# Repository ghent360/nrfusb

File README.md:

# Theory of operation #

A transmitter and receiver must be programmed with identical 32 bit
radio IDs.  With those IDs, the transmitter and receiver select a set of
23 channels using a pseudorandom number generator.

## Channel Selection ##

23 channels are selected.  Their selection and order is determined as
follows:

The pseudorandom number function is:

```
prn = (prn * 0x0019660D) + 0x3C6EF35F
```

A potential channel is `prn % 125`.  Channels are evaluated in order such that:

* The prn is evaluated once, then modulo 125 to generate a candidate
  channel

* No channel is repeated.  If the candidate channel has already been
  selected, the candidate is discarded.

* No more than a certain number of channels can be chosen from each of
  the different bands.  If a candidate channel would exceed this
  limit, it is discarded.
  * 0-31: 6
  * 32-63: 6
  * 64-95: 6
  * 96-125: 5

## Transmission ##

The transmitter and receiver use the nrf24l01 Enhanced ShockBurst with
the following parameters:

* 5 byte address field, the channel ID mapped into 5 bytes as below
* Dynamic payload length
* 2 byte CRC
* No automatic retransmission
* Auto acknowledgement
* 1Mbps data rate

The transmitter sends a new packet every 20ms, waiting 1ms for an
acknowledgement with data on the same channel.  Each transmitted
packet advances to the next channel in the channel selected list,
wrapping around.

## Reception ##

To initially lock onto a transmitter, the receiver picks a random
channel from the list and listens for 20 channel change times (0.4s).
If no packet is received, it then moves to the next channel in the
list and waits another 20 time periods, continuing this process until
a packet is received.  Once a packet is received it switches to the
following procedure.

In normal reception, immediately after receiving and acknowledging a
packet, the receiver switches to the next channel in the list.  It
waits at least 22ms for the next packet to be received.  If no packet
is received, then the channel is switched to the next one and
listening recommences.  If 5 packets in a row are missed, then the
receiver returns to the initial lock procedure.

## ID selection ##

The ShockBurst address is derived from the 32 bit ID as follows.

1100bbbb bbbbbbbH bbbbbbbH bbbbbbbH bbbbbbH

`b` is a bit from the 32 bit ID.

The `H` bits are selected to be the opposite of whatever the
preceeding bit was.

Rationale: The highest bits are defined to be distinct from the
preamble, which consists of alternating bits.  The H bits are present
to reduce the likelihood that random noise will cause the address to
be identified by the baseband receiver.

## Scheduling ##

The transmitter and receiver have 15 different "slots" to hold
outgoing data.  Each can be configured for a different priority or
transmission rate and each can hold up to 16 bytes of data.

The transmission rate/priority is configured by providing a 32 bit
bitmask denoting in which timeslots this slot should be sent.
Configuring an infeasible set of slots will result in unspecified data
being sent at a lower rate.

A priority of 0 is the default, which signifies that the slot should
not be transmitted.  0xffffffff implies it should be sent every
timeslot.  0x55555555 would be every other timeslot, etc.

The data in a slot will continue to be transmitted at the specified
frequency whether or not it has been updated by the client recently.

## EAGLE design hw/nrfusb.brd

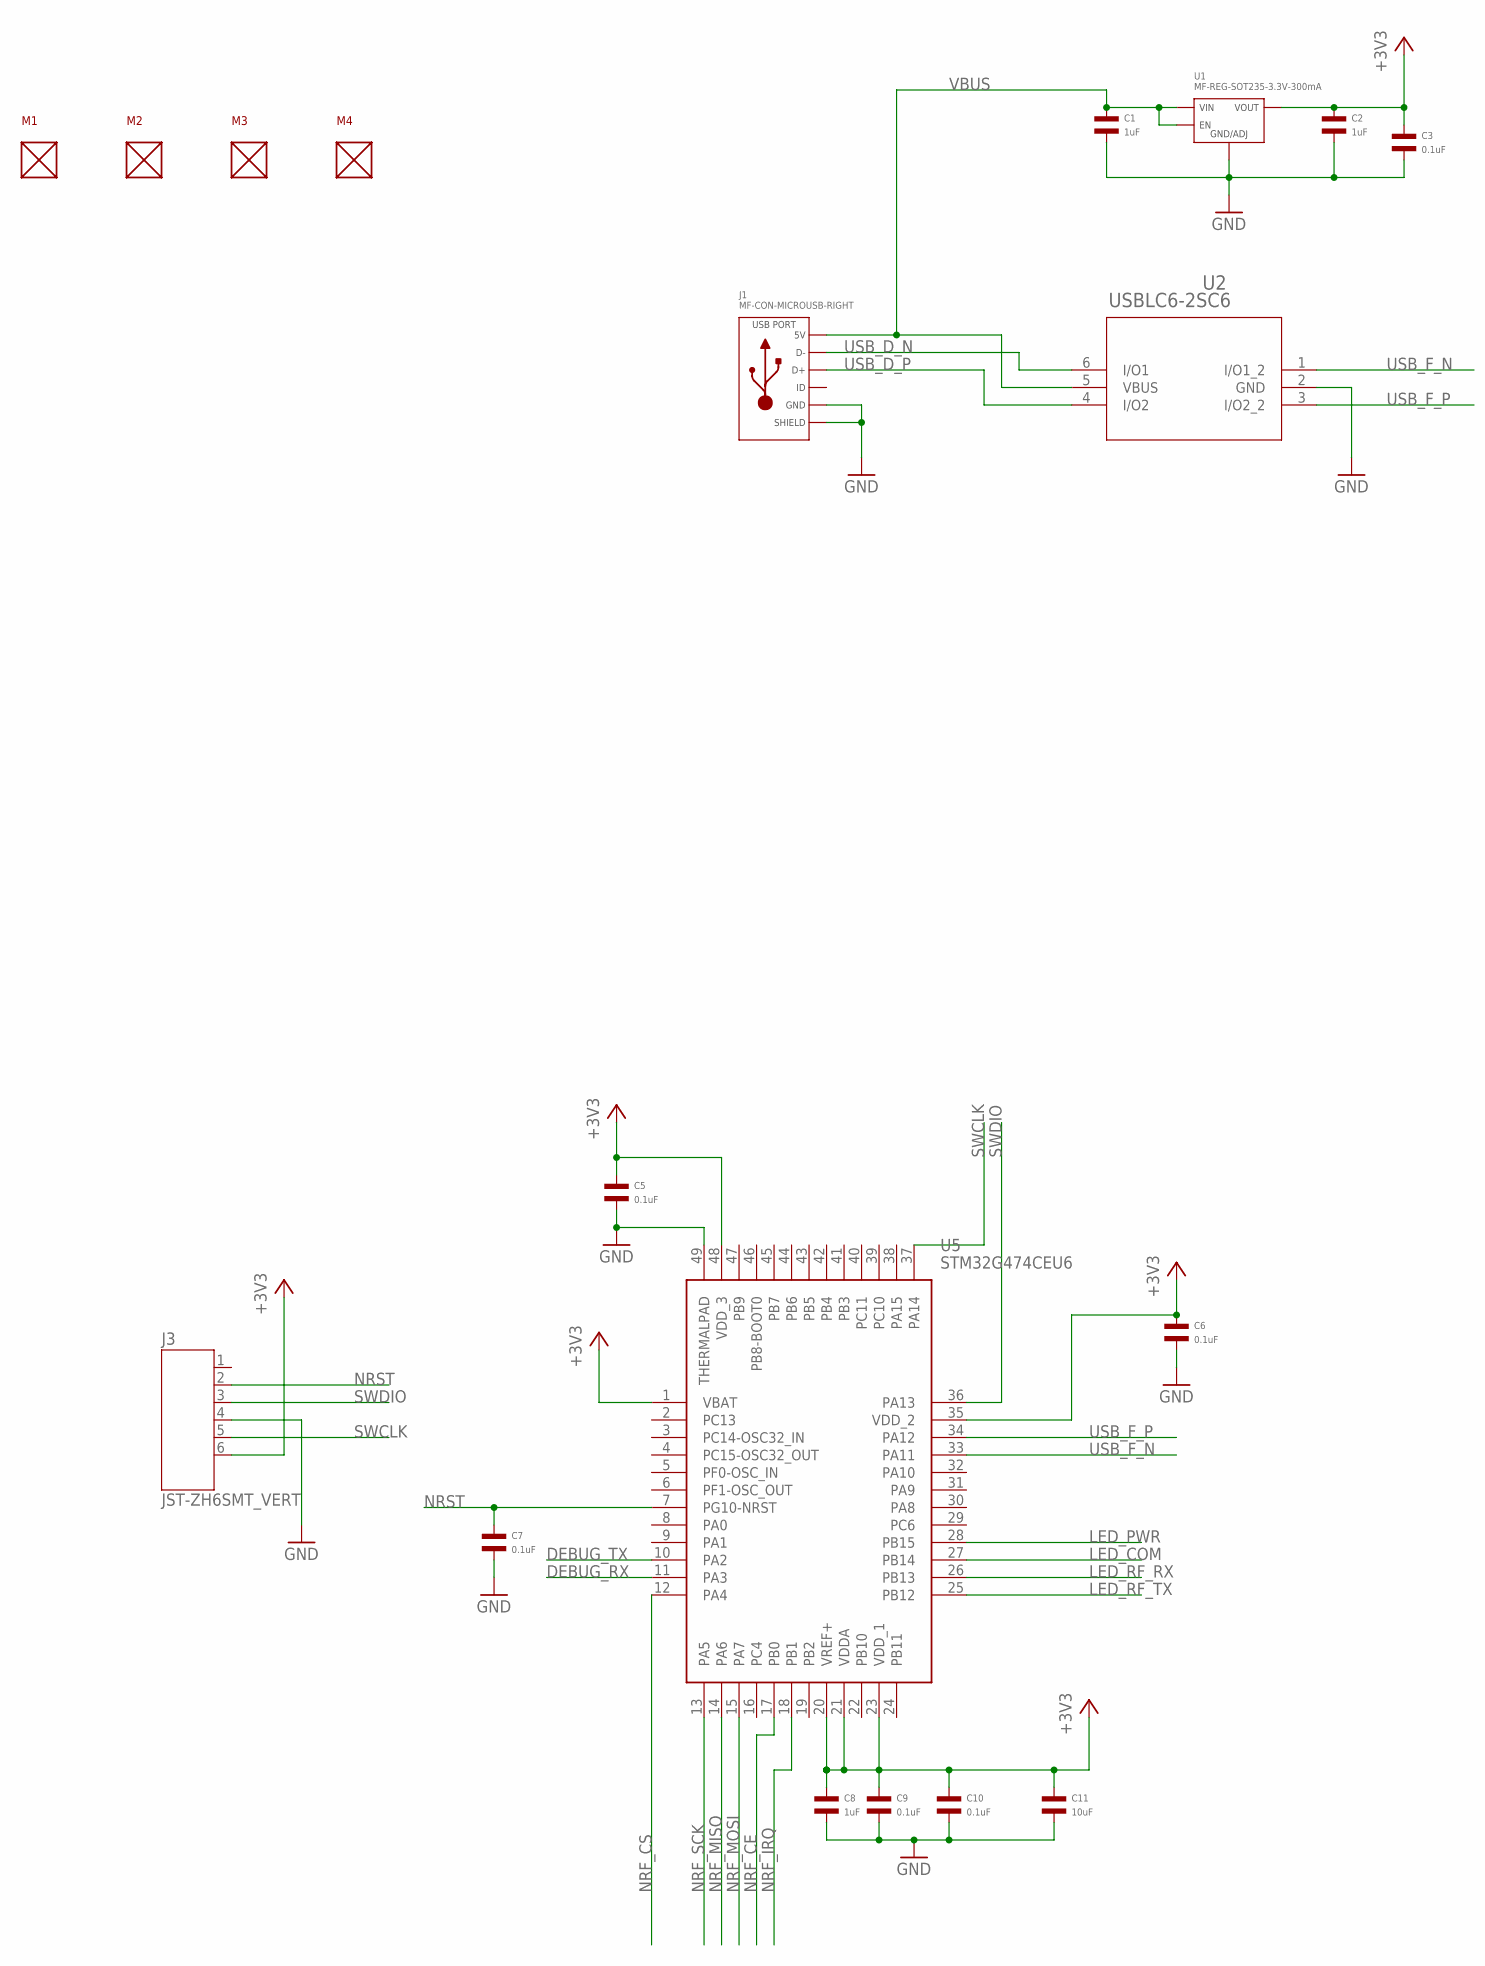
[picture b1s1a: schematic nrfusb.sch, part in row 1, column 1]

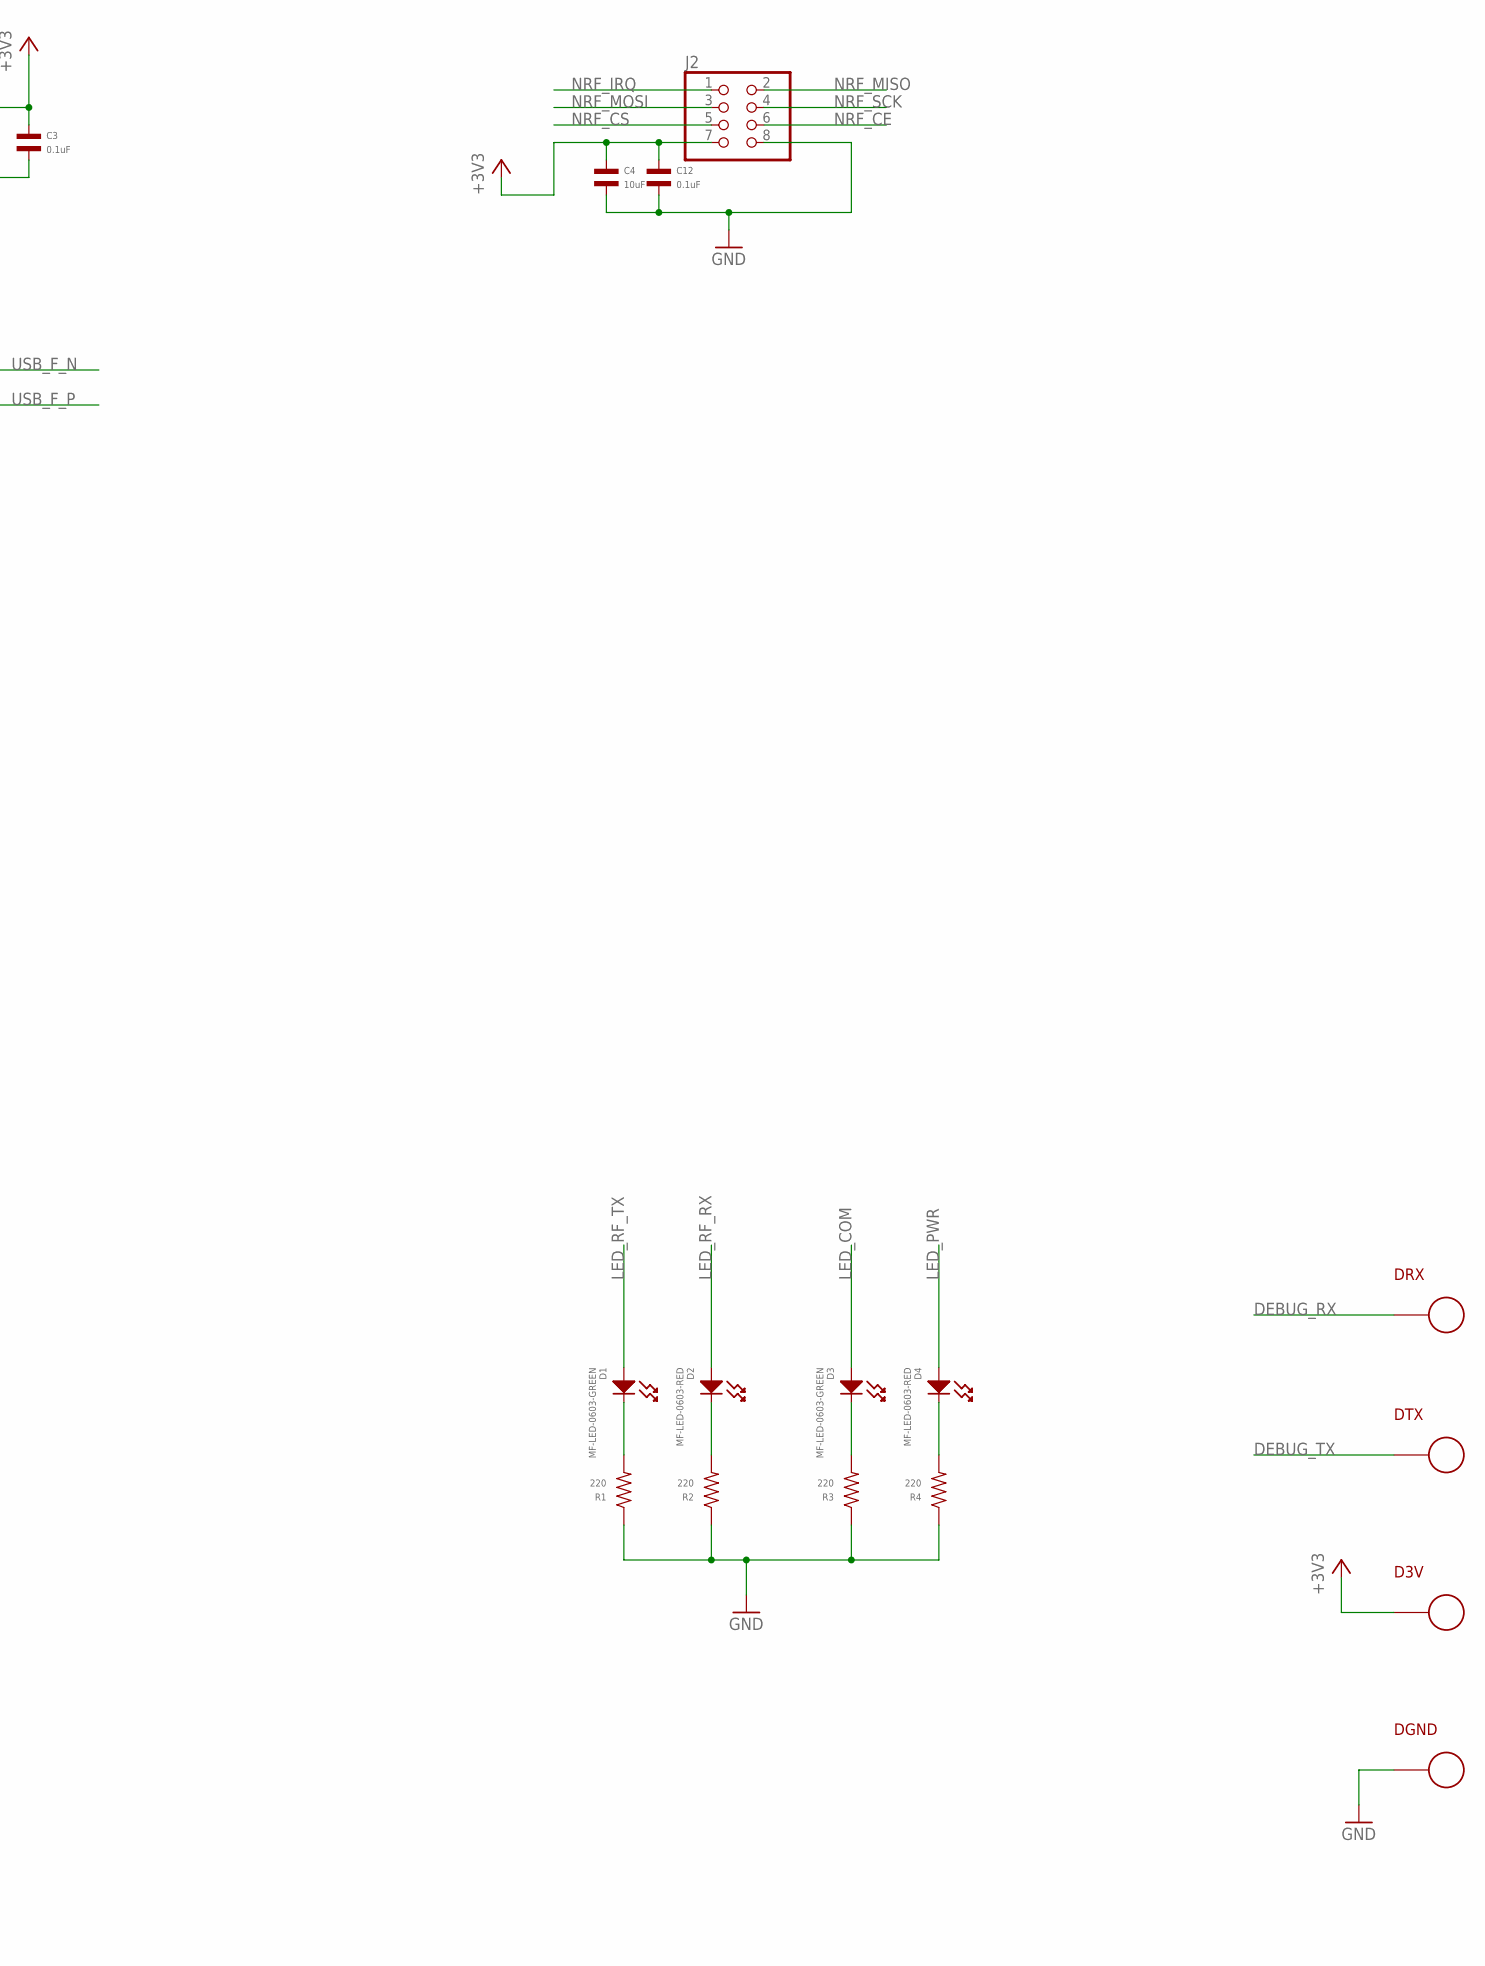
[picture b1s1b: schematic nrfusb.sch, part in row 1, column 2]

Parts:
C1, C2, C8: 1uF; C0603; MPN MF-CAP-0603-1uF
C3, C5, C6, C7, C9, C10, C12: 0.1uF; C0402; MPN MF-CAP-0402-0.1uF
C4, C11: 10uF; C1206; MPN MF-CAP-1206-10uF
D1, D3: MF-LED-0603-GREEN; LED0603
D2, D4: MF-LED-0603-RED; LED0603
D3V: PAD24AWG_PAD; 24AWG_PAD
DGND: PAD24AWG_PAD; 24AWG_PAD
DRX: PAD24AWG_PAD; 24AWG_PAD
DTX: PAD24AWG_PAD; 24AWG_PAD
J1: MF-CON-MICROUSB-RIGHT; MICROUSB-RIGHT
J2: PINHD-2X4; 2X04; MPN 61300821121
J3: JST-ZH6SMT_VERT; JST_B6B-ZR-SM4-TF(LF)(SN); MPN B6B-ZR-SM4-TF(LF)(SN)
M1, M2, M3, M4: MOUNT; M2.5MOUNT
R1, R2, R3, R4: 220; R0402; MPN MF-RES-0402-220
U1: MF-REG-SOT235-3.3V-300mA; SOT-23-5
U2: USBLC6-2SC6; SOT23-6L; MPN USBLC6-2SC6
U5: STM32G474CEU6; QFN50P700X700X60-49N; MPN STM32G474CEU6

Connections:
+3V3: C2.P$1, C3.P$1, C4.P$1, C5.P$1, C6.P$1, C8.P$1, C9.P$1, C10.P$1, C11.P$1, C12.P$1, D3V.P$1, J2.7, J3.6, U1.P$5 (VOUT), U5.1 (VBAT), U5.20 (VREF+), U5.21 (VDDA), U5.23 (VDD_1), U5.35 (VDD_2), U5.48 (VDD_3)
DEBUG_RX: DRX.P$1, U5.11 (PA3)
DEBUG_TX: DTX.P$1, U5.10 (PA2)
GND: C1.P$2, C2.P$2, C3.P$2, C4.P$2, C5.P$2, C6.P$2, C7.P$2, C8.P$2, C9.P$2, C10.P$2, C11.P$2, C12.P$2, DGND.P$1, J1.5 (GND), J1.S1 (SLD), J1.S2 (SLD), J1.S3 (SLD), J1.S4 (SLD), J1.S5 (SLD), J1.S6 (SLD), J2.8, J3.4, R1.P$1, R2.P$1, R3.P$1, R4.P$1, U1.P$2 (GND/ADJ), U2.2 (GND), U5.49 (THERMALPAD)
LED_COM: D3.ANODE, U5.27 (PB14)
LED_PWR: D4.ANODE, U5.28 (PB15)
LED_RF_RX: D2.ANODE, U5.26 (PB13)
LED_RF_TX: D1.ANODE, U5.25 (PB12)
unnamed: D1.CATHODE, R1.P$2
unnamed: D2.CATHODE, R2.P$2
unnamed: D3.CATHODE, R3.P$2
unnamed: D4.CATHODE, R4.P$2
NRF_CE: J2.6, U5.17 (PB0)
NRF_CS: J2.5, U5.12 (PA4)
NRF_IRQ: J2.1, U5.18 (PB1)
NRF_MISO: J2.2, U5.14 (PA6)
NRF_MOSI: J2.3, U5.15 (PA7)
NRF_SCK: J2.4, U5.13 (PA5)
NRST: C7.P$1, J3.2, U5.7 (PG10-NRST)
SWCLK: J3.5, U5.37 (PA14)
SWDIO: J3.3, U5.36 (PA13)
USB_D_N: J1.2 (D-), U2.6 (I/O1)
USB_D_P: J1.3 (D+), U2.4 (I/O2)
USB_F_N: U2.1 (I/O1_2), U5.33 (PA11)
USB_F_P: U2.3 (I/O2_2), U5.34 (PA12)
VBUS: C1.P$1, J1.1 (5V), U1.P$1 (VIN), U1.P$3 (EN), U2.5 (VBUS)

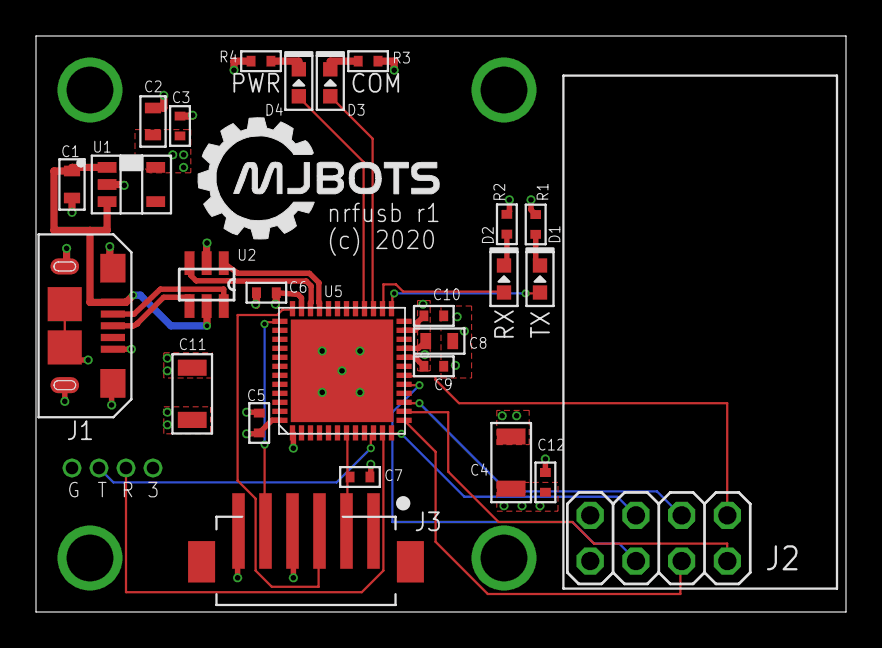
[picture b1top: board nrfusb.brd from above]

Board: 4 copper layers, 45.0 x 32.0 mm, 34 parts (0 on the bottom side), 26 nets.

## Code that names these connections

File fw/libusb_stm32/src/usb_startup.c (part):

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    _BMD(RCC->CFGR, RCC_CFGR_SW, RCC_CFGR_SW_PLL);
    _WVL(RCC->CFGR, RCC_CFGR_SWS, RCC_CFGR_SWS_PLL);

    /* Enabling USB PA11 PA12 AF 0x0E.
     * This is still undocumented in the 7th!! revision of the datasheet.
     * Thank you, mo***rs from ST for extra 5 hrs of debugging.
     */
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    _WVL(RCC->CFGR, RCC_CFGR_SWS, RCC_CFGR_SWS_PLL);
#endif    
    #if defined(USBD_PRIMARY_OTGHS)
    /* enabling GPIOB and setting PB13, PB14 and PB15 to AF11 (USB_OTG2FS) */
    _BST(RCC->AHB1ENR, RCC_AHB1ENR_GPIOBEN);
    #if defined(USBD_VBUS_DETECT)
    _BST(GPIOB->AFR[1], (0x0C << 24) | (0x0C << 28) | (0x0C << 20));
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    _BMD(GPIOB->MODER, (0x03 << 28) | (0x03 << 30), (0x02 << 28) | (0x02 << 30));
    #endif //defined(USBD_VBUS_DETECT)
    #else  //defined(USBD_PRIMARY_OTGHS)
    /* enabling GPIOA and setting PA11 and PA12 to AF10 (USB_FS) */
    _BST(RCC->AHB1ENR, RCC_AHB1ENR_GPIOAEN);
    _BST(GPIOA->AFR[1], (0x0A << 12) | (0x0A << 16));
    _BMD(GPIOA->MODER, (0x03 << 22) | (0x03 << 24), (0x02 << 22) | (0x02 << 24));
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    /* switching to PLL */
    _BMD(RCC->CFGR, RCC_CFGR_SW, RCC_CFGR_SW_PLL);
    _WVL(RCC->CFGR, RCC_CFGR_SWS, RCC_CFGR_SWS_PLL);
    /* enabling GPIOA and setting PA11 and PA12 to AF10 (USB_FS) */
    #if defined(USBD_PRIMARY_OTGHS)
    _BST(RCC->AHB1ENR, RCC_AHB1ENR_GPIOBEN);
    _BST(GPIOB->AFR[1], (0x0C << 24) | (0x0C << 28));
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    _BST(RCC->CRRCR, RCC_CRRCR_HSI48ON);
    _WBS(RCC->CRRCR, RCC_CRRCR_HSI48RDY);
    _BMD(RCC->CCIPR, RCC_CCIPR_CLK48SEL, 0);
    /* setup PA11 PA12 to AF10 (USB FS) */
    _BST(RCC->AHB2ENR, RCC_AHB2ENR_GPIOAEN);
    _BMD(GPIOA->MODER, (0x03 << 22) | (0x03 << 24), (0x02 << 22) | (0x02 << 24));
    _BST(GPIOA->AFR[1], (0x0A << 12) | (0x0A << 16));
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    _BST(RCC->CRRCR, RCC_CRRCR_HSI48ON);
    _WBS(RCC->CRRCR, RCC_CRRCR_HSI48RDY);
    _BMD(RCC->CCIPR, RCC_CCIPR_CLK48SEL, 0);
    /* setup PA11 PA12 to AF10 (USB FS) */
    _BST(RCC->AHB2ENR, RCC_AHB2ENR_GPIOAEN);
    _BMD(GPIOA->MODER, (0x03 << 22) | (0x03 << 24), (0x02 << 22) | (0x02 << 24));
    _BST(GPIOA->AFR[1], (0x0A << 12) | (0x0A << 16));
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    _WBS(RCC->CR, RCC_CR_HSI48RDY);
    _BMD(RCC->D2CCIP2R, RCC_D2CCIP2R_USBSEL, 3 << RCC_D2CCIP2R_USBSEL_Pos);

    /* enabling GPIOA and setting PA11 and PA12 to AF10 (USB_FS) */
    _BST(RCC->AHB4ENR, RCC_AHB4ENR_GPIOAEN);
    _BMD(GPIOA->MODER, (0x03 << 22) | (0x03 << 24), (0x02 << 22) | (0x02 << 24));
    _BST(GPIOA->AFR[1], (0x0A << 12) | (0x0A << 16));
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
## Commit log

2019-10-08 Initialize with a fork of fdcanusb
2019-10-08 Nominally complete board and schematic
2020-02-18 Update with correct stm32 pinout
2020-02-18 Auto-route
2020-02-18 Remove an autogenerated file
2020-02-18 Fine tweak silks
2020-03-06 Stub firmware
2020-03-07 Change the USB name and stub in USB CDC support
2020-03-07 Configure the nrf on power up
2020-03-07 Basic NRF operations (not seeming to work yet)
2020-03-07 Make flash.sh actually work
2020-03-07 Basic operation without automatic ack working
    There are probably some things can be simplified back still.
2020-03-09 Get things besides auto-ack working
2020-03-12 Add nrf24l01+ datasheet
2020-03-12 Auto-ack works with bidirectional data!
2020-03-13 Update TODO
2020-03-16 Support online channel selection
2020-03-16 Refactor pin configuration to enable direct pass through
2020-03-17 Beginnings of the slot protocol implementation
2020-03-17 Actually look in the correct place for sources
2020-03-17 First draft of an interface and misc bug fixes
    This currently has raw vs. slot selected at compile time. It also
    doesn't work properly yet, but does transmit "something".
2020-03-18 Fix enough bugs to get sending and receiving working
2020-03-18 Set SPI frequency to 10MHz
2020-03-18 Use the correct frequency for the millisecond timer
2020-03-18 No longer die for errors
2020-03-18 Make parsing of slots greater than 0 actually work
2020-03-18 Get priority selection working and fix other bugs
2020-04-01 Add a udev rule
2020-04-30 Factor to be closer to supporting multiple receivers
    At the moment, still only one remote is supported though
2020-04-30 Actually support transmitting to multiple receivers
    Also, add a transmit timeout. At least some transmission must occur
    every N ms or all of the channels get their priority set to 0.
2020-04-30 Fix a race when associating remotes
    If the response from a remote came in after more than 1ms, it would be
    associated with the next remote.
2022-12-28 Update libusb_stm32 to the latest version. Make code compile for STM32F4.
2022-12-28 Fix issues with no NRF module connected.
2022-12-28 Add file to initialize the USB pins on STM32F4.
2022-12-28 Comment on the disabled code.
2022-12-28 Add KiCAD schematics and PCB, fix clock source for the F4 board.
2022-12-28 Switch to my copy of rules_mbed.
2022-12-28 Update to my most recent version of rbed_rules. Update bazel version. Update mjlib version. Fix build issues.
2022-12-28 Fix STM32F1 compile issues. Sadly the binary is too big for the bluepill.
2022-12-28 Update NRF module pins.

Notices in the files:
fw/libusb_stm32/src/usb_startup.c:
Copyright ©2016 Dmitry Filimonchuk <dmitrystu[at]gmail[dot]com>
Licensed under the Apache License, Version 2.0 (the "License");
hw/nrfusb.sch:
(c) 2020 Josh Pieper, jjp@pobox.com
Licensed under the Apache 2.0 License
https://www.apache.org/licenses/LICENSE-2.0
